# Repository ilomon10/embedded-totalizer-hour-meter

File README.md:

# Totalizer Hour Meter

An ESP32-based **engine hour meter and totalizer** for 12/24 V vehicles and machines. It counts engine run hours from the alternator signal, counts totalizer pulses, and measures vibration, roll/pitch and compass heading with an IMU. Counters survive power cuts in the ESP32's flash and the EEPROM (either one is enough), time is kept in UTC on an RTC, and everything is reported as compact [SensorFrame](sensorframe/README.md) binary frames over USB, UART or Bluetooth SPP to the `hour-meter` configurator.

Firmware version: **2.7.0** (see `kFirmwareVersion` in [`Protocol.h`](esp32/lib/App/src/Protocol.h)).

```
 Vehicle 12/24 V ──► main board ───────────────────────────────┐
 L / D+ (run)─┐      PTC + reverse diode + TVS → LM2596 (5 V)  │
 Pulse input ─┴────► PC817 isolated inputs ───► GPIO27 / GPIO26│
                                                               ▼
                    ┌──────────── ESP32 ───────────────────────────┐
                    │ AT24C256 EEPROM · DS3231 RTC · MPU-6500 IMU  │
                    │ (I2C, all optional and hot-pluggable)        │
                    └───────────────┬──────────────────────────────┘
                                    │ SensorFrame (TLV + CRC16, COBS)
                       USB / UART / Bluetooth SPP
                                    ▼
                    configurator/  hour-meter: TUI · read · commands
```

## Repository map

| Path | What it is |
|---|---|
| [`esp32/`](esp32/README.md) | PlatformIO firmware. Envs: `esp32dev` (firmware for the devboard), `can-board` (the same firmware for the main board), `bench` (module test firmware), `native` (unit tests on the PC) |
| [`configurator/`](configurator/README.md) | `hour-meter` (Bun, released as a standalone binary): full-screen TUI, live reader (`read`), single commands (`get`, `set`, ...), firmware update over USB (`firmware`) and the `DeviceClient` library |
| [`sensorframe/`](sensorframe/README.md) | The wire format: [SPEC.md](sensorframe/SPEC.md), header-only C++ library (`arduino/`), zero-dependency npm package (`js/`), shared golden test vectors |
| [`schematic/hour-meter-board/`](schematic/hour-meter-board/README.md) | Main board (KiCad): ESP32-WROOM-32E, 9–30 V supply and one Molex Micro-Fit 2 × 8 harness plug with CAN, RS232, RS485, isolated DIN1/DIN2, AIN1, DOUT1 and a 5 V sensor supply; MPU-6500 + LIS3MDL, RTC, EEPROM, USB-C, GPS and Qwiic ports. 100 × 100 mm, 2 layers, routed by hand; JLCPCB order files in `production/`, bring-up guide in `BRINGUP.md` |
| [`schematic/hour-meter-devboard/`](schematic/hour-meter-devboard/README.md) | Devboard (KiCad): 88 × 91 mm, 2-layer, through-hole carrier for ready-made modules from Indonesian shops: ESP32 DevKit V4 (USB-C), 817 opto module, GY-9250, DS3231 ZS-042, AT24C256 and a GY-271 compass. Runs from the DevKit's USB-C; Gerbers, a BOM with local shop names, LCSC lists and a 1:1 fit-check PDF in `production/` |
| [`schematic/fault-analysis/`](schematic/fault-analysis/README.md) | ngspice simulations: the main board's ports and harness (`microfit_can.py`), and supply transients, reverse polarity, shorted outputs and miswired connectors for the circuits both boards use (`faults.py`) |
| `schematic/datasets/` | Datasheets (LIS3MDL, MAX13223E) |
| [`simulator/`](simulator/README.md) | Bun device simulator: the real protocol on a virtual serial port (socat), TCP or stdio, with fault scenarios, the Bluetooth lock, and a web UI (`--web`): every value live, a 3D bench, and a truck/plane on an OpenStreetMap map with IMU-only dead reckoning. For driver development without hardware |
| `canbus/` | `can.sh`: CANable2 (slcan) helper for can-utils: `up [rate] [--tx]`, `down`, `scan [seconds]`, `status`. Listen-only by default |

Older board versions (the rev A and rev C module carriers, the rev B main board and its 2-layer, compact, LM2596, I/O and Micro-Fit versions, the auto-routed CAN board and the PSU-B supply) were removed on 2026-11-04. They are in the git history at commit d35ef2d.

## Hardware at a glance

Two boards run the same firmware:

| Board | What it is | Firmware build |
|---|---|---|
| [Main board](schematic/hour-meter-board/README.md) | everything on one PCB, made and assembled by JLCPCB: 9–30 V supply, one harness plug with CAN, RS232, RS485, DIN1/DIN2, AIN1, DOUT1 and a 5 V sensor supply, MPU-6500 + LIS3MDL IMU | `pio run -e can-board` |
| [Devboard](schematic/hour-meter-devboard/README.md) | ready-made modules on a through-hole carrier, powered from USB: ESP32 DevKit V4, 817 opto module, GY-9250, DS3231, AT24C256, GY-271 compass | `pio run -e esp32dev` (the default) |

Both: AT24C256 EEPROM (0x50) · DS3231 RTC (0x68) · MPU-6500/MPU9250 IMU (**0x69**, AD0 high) · alternator input GPIO27 · pulse input GPIO26 (through PC817 optocouplers, outputs active LOW) · Bluetooth Classic SPP (off by default, PIN-locked). The UART link is GPIO16/17 on the devboard and the RS232 port on the main board. Module wiring and the required resistor changes: [esp32/docs/WIRING.md](esp32/docs/WIRING.md).

Before ordering the main board, check part stock with `./scripts/jlc-stock.ts <bom.csv>`.

## Quick start

Prerequisites: [PlatformIO](https://platformio.org/) CLI (firmware), [Bun](https://bun.com) 1.4.4 or newer (configurator, simulator, scripts, doc checks). Optional: socat (simulator tty), Node.js ≥ 18 (only for the `sensorframe/js` npm package tests), KiCad 8+ (hardware), can-utils (`canbus/can.sh`). Users who only need the tools can download the `hour-meter` / `hour-meter-sim` binaries (Linux x64, Windows x64) from the releases page instead.

```bash
# Firmware
cd esp32
pio run -e esp32dev -t upload       # build + flash (devboard)
pio run -e can-board -t upload      # the same, for the main board

# Host tools
cd ../configurator                  # or download hour-meter from the releases page
bun install                         # once: the TUI's packages
bun run start --demo                # try the TUI with a simulated device (no hardware)
bun run start /dev/ttyUSB0          # the real device
bun run start set-time --port /dev/ttyUSB0   # set the RTC from the PC clock (UTC)
bun run start get hour --port /dev/ttyUSB0   # read the hour meter
bun run start firmware flash --port /dev/ttyUSB0   # update to the newest release (no PlatformIO needed)
```

No device at hand? `bun run start --demo` runs a simulated one inside the configurator, or `cd simulator && bun install && bun run start` creates one at `/tmp/ttyHourMeter` for any tool or driver.

Testing loose modules before soldering: `pio run -e bench -t upload`, see [TESTING-MODULES.md](esp32/docs/TESTING-MODULES.md).

## Tests and checks

```bash
cd esp32 && pio test -e native            # firmware unit tests with fake chips (ASan + UBSan)
cd esp32 && pio check -e esp32dev         # clang-tidy static analysis
./esp32/scripts/check-docs.ts             # docs, host tag table and firmware tables agree
cd configurator && bun run test           # hour-meter: commands, DeviceClient, the TUI
cd sensorframe/js && npm test             # SensorFrame JS library
make -C sensorframe/arduino/test          # SensorFrame C++ library on the desktop
cd simulator && bun run test              # simulator: firmware golden frames, frame catalog, command rules
bun test scripts/                         # release notes and asset names, JLCPCB BOM parsing
cd configurator && bun check && bun run lint && bun fmt --check   # types, lint, format (the same in simulator/)
```

## Releasing

One GitHub release, tagged `v<VERSION>` (the [`VERSION`](VERSION) file), carries all three parts: the firmware images, the `hour-meter` binaries and the `hour-meter-sim` binaries. Each part keeps its own version (`kFirmwareVersion` in `Protocol.h`, `TOOL_VERSION` in `configurator/src/version.ts`, `SIM_VERSION` in `simulator/main.ts`), and the release notes show them side by side. [`scripts/release.ts`](scripts/release.ts) does it all:

```bash
./scripts/release.ts --dry-run              # what it would run, plus the release notes; changes nothing
./scripts/release.ts                        # checks, tests, builds, asks, then tags, pushes and publishes
./scripts/release.ts --bump minor           # next release: VERSION 1.0.0 -> 1.1.0 in a commit first
./scripts/release.ts --notes notes.md --draft   # your own notes ("# Title" first line), as a draft
```

It releases HEAD (or `--ref <commit>`). It tests and builds that exact commit in a temporary git worktree, and puts the files, one `SHA256SUMS` and `NOTES.md` in `.release/v<VERSION>/`. It asks before anything leaves your machine. Afterwards it downloads the release and checks `SHA256SUMS`, both binaries' `--version` and the firmware image.

It stops before changing anything if:
- you're not on `main`;
- a released folder has uncommitted changes;
- `gh` isn't logged in;
- `origin/main` has commits you lack;
- the tag or release already exists. Use `--bump` in that case.

It warns when a part changed since the previous release but still has the same version. Without `--notes`, the notes are generated from the Conventional Commit messages since the previous release. Releases before 1.0.0 were separate per part (`firmware-v*`, `configurator-v*`, `simulator-v*`).

`hour-meter firmware` finds the firmware in a release by its file name, `hour-meter-<firmware version>-esp32dev-merged.bin`, and checks it against the release's `SHA256SUMS`. Keep both. The configurator's tests fail if `assetNames()` in `scripts/release-lib.ts` stops matching.

## Documentation

| You are… | Read |
|---|---|
| Building an app that talks to the device | [INTEGRATION-GUIDE.md](esp32/docs/INTEGRATION-GUIDE.md) + [SensorFrame SPEC.md](sensorframe/SPEC.md) |
| Writing a driver: exact bytes of every frame | [FRAME-CATALOG.md](esp32/docs/FRAME-CATALOG.md) |
| Developing without hardware | [simulator/README.md](simulator/README.md) |
| Wiring the hardware | [main board](schematic/hour-meter-board/README.md) and its [bring-up](schematic/hour-meter-board/BRINGUP.md), [devboard](schematic/hour-meter-devboard/README.md), [WIRING.md](esp32/docs/WIRING.md) (the devboard's modules) |
| Working on the firmware | [ARCHITECTURE.md](esp32/docs/ARCHITECTURE.md), [CODING-STANDARD.md](esp32/docs/CODING-STANDARD.md) |
| A TypeScript developer new to C++ | [CPP-FOR-TYPESCRIPT.md](esp32/docs/CPP-FOR-TYPESCRIPT.md) |
| Curious how data survives power cuts | [STORAGE.md](esp32/docs/STORAGE.md), [EEPROM-LAYOUT.md](esp32/docs/EEPROM-LAYOUT.md) |
| Setting up the IMU | [CALIBRATION.md](esp32/docs/CALIBRATION.md) |
| Using the TUI, CLI or Bluetooth | [configurator/README.md](configurator/README.md) |
| Using SensorFrame in another project | [sensorframe/README.md](sensorframe/README.md) |

## Design rules

- **Time is UTC only.** The device stores a Unix epoch with no timezone; host tools convert for display.
- **`esp32/lib/App/src/Protocol.h` is the single source of truth for tags.** After any protocol change, run `./esp32/scripts/check-docs.ts`, update `configurator/src/tags.ts`, port the change to `simulator/src/frames.ts`, and run `bun run test` there (it fails until the simulator's frames match the firmware's golden frames again).
- **USB is the recovery path:** fixed at 115200 baud and always accepts commands. `uartBaud` only affects the UART pins.
- **The stores (ESP32 flash, EEPROM) hold only counters, calibration and settings**, never sample logs. Filtering (Kalman) runs in RAM.

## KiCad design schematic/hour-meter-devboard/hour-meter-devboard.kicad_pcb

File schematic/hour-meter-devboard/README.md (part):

# Hour Meter devboard: ESP32 V4 module carrier with compass (rev D)

An 88 × 91 mm, 2-layer, through-hole carrier for ready-made modules from Indonesian electronics shops:
- the ESP32 DevKit V4 (USB-C, 38 pins);
- the 2-channel PC817 "817 Module";
- the GY-9250 (MPU9250/6500);
- the DS3231 ZS-042 RTC;
- the AT24C256 EEPROM;
- the GY-271 compass (QMC5883L or HMC5883L).

The DevKit's USB-C is the only supply. Vehicle wires go to screw terminals, and every other part is a common THT part.

The devboard is rev D of the module carrier: rev C plus a socket for a GY-271 compass, on a board 20 mm taller ([Changes from rev C](#changes-from-rev-c)). GY-9250 modules sold locally often carry an MPU6500, which has no compass; the GY-271 always has one. The firmware pins are those of the earlier carriers, so it runs the `esp32dev` build.

| | |
|---|---|
| Schematic | `hour-meter-devboard.kicad_sch` (PDF: `hour-meter-devboard.pdf`, picture: `hour-meter-devboard.png`) |
| PCB | `hour-meter-devboard.kicad_pcb` (pictures: `hour-meter-devboard-pcb.png`, `hour-meter-devboard-3d.png`) |
| Ready to order | `production/hour-meter-devboard-gerbers.zip` (Gerbers + drill files) |
| Parts list | `production/hour-meter-devboard-bom.csv`: what to buy, with the search terms local shops use |
| LCSC order | `production/hour-meter-devboard-lcsc-upload.csv` for LCSC's BOM tool, and `-lcsc-parts.csv` with part numbers, stock and fit notes ([Buying the parts](#buying-the-parts)) |
| Check before ordering | `production/hour-meter-devboard-fit-check-1to1.pdf`: print at 100 % and lay the modules on it |
| Custom parts | `hour-meter-modules.kicad_sym` (symbols), `hour-meter-modules.pretty/` (footprints, from `tools-gen-footprints.py`) |
| Input simulations | [fault analysis](../fault-analysis/README.md), *V4 module carrier* group |
| Firmware | `pio run -e esp32dev -t upload` in `esp32/` (the default build); module wiring and tests in [WIRING.md](../../esp32/docs/WIRING.md) |

**Checks at release (rev D, 2026-11-04, after the [hand edits and their audit](#hand-edits-and-audit)):**
- ERC: 0 errors, 0 warnings.
- DRC: 0 errors, 0 warnings, 0 unconnected, 0 schematic mismatches. JLCPCB's 2-layer limits pass too.
- 2 copper layers; the Gerbers hold copper L1/L2 only.
- Logic copper stays at least 3.8 mm from vehicle copper (the netclass minimum is 0.8 mm).

## What is on the board

| Ref | Part | Connects to |
|---|---|---|
| U1 | ESP32 DevKit V4 on 2 × 19 sockets. The antenna overhangs the top edge; the USB-C end points down | everything |
| M1 | 817 module on 4 M3 standoffs, above its own input protection | J1/J2 inputs → GPIO27/GPIO26 |
| M2, M3, M4 | DS3231, AT24C256 and GY-9250, lying flat on sockets, chip side up | I2C, 3V3 |
| M5 | GY-271 compass, lying flat on a 1×5 socket in the bottom strip, far from the DevKit and the RTC battery | I2C, 3V3; DRDY not connected |
| J1, J2 | Screw terminals: alternator (D+/L) and 12/24 V pulse; pin 2 = vehicle ground | M1 inputs |
| J3 | Spare 2 × 5 header: UART2 and five GPIOs, 3V3 through F1 | U1 |
| D5 | Status LED (green, 3 mm) | GPIO2 |

| ESP32 pin | Use | | I2C address | Device |
|---|---|---|---|---|
| GPIO21 / 22 | I2C SDA / SCL (100 kHz, module pull-ups) | | 0x50 | AT24C256 (A0–A2 = GND) |
| GPIO27 | ALT_IN, from J1 through 817 channel 1 (LOW = running) | | 0x68 | DS3231 |
| GPIO26 | PULSE_IN, from J2 through 817 channel 2 | | 0x57 | AT24C32 on the ZS-042 (unused) |
| GPIO17 / 16 | UART2 TX / RX on J3 | | 0x69 | MPU9250 / 6500 (AD0 = 3V3) |
| GPIO4, 13, 25, 32, 33 | Spare, on J3 | | 0x0C | AK8963 magnetometer (MPU9250 only) |
| GPIO2 | Status LED D5, active high. **The firmware doesn't drive it yet** | | 0x0D | QMC5883L on the GY-271 (most modules sold today) |
| | | | 0x1E | HMC5883L on older GY-271 modules |

J3, seen from the top (labels on the silkscreen, full pinout on the back):

```
upper row   2 GND    4 RX2 (IO16)   6 IO13   8 IO32   10 GND
lower row   1 3V3*   3 TX2 (IO17)   5 IO4    7 IO25    9 IO33        * through F1, 0.1 A PTC
```

J3 is for 3.3 V logic only, and nothing on it is vehicle-proof. GPIO12, 14 and 15 are left off: 12 and 15 are boot strapping pins, and 14 puts out PWM at boot.

## ⚠ Measure before you order

The module footprints use typical clone dimensions. **Print `production/hour-meter-devboard-fit-check-1to1.pdf` at 100 %** (no "fit to page"). Check that the board outline measures 88 × 91 mm, then lay each module on its outline: the pins must land on the pads. If one doesn't fit, change its numbers in `tools-gen-footprints.py` and regenerate (see [the end](#regenerating-after-a-change)).

| Part | Assumed | Check |
|---|---|---|
| ESP32 DevKit V4 | 2 × 19 pins, rows **25.4 mm apart** (Espressif's DevKitC footprint), antenna about 7 mm beyond pin 1 | Some narrow 38-pin clones use 22.86 mm |
| 817 module | 38 × 29 mm, 4 × M3 holes **32 × 24 mm** apart | Only one seller lists the hole spacing |
| GY-9250 | 15.5 × 25.5 mm, 10 pins down the left edge; M3 holes 12 mm right of the pins, 0.5 mm and 21.6 mm below pin 1 | The holes come from a photo. If they don't line up, leave the two standoffs out |
| DS3231 ZS-042 | 38 × 22 mm, 1 × 6 pins on one short edge, 32K at the top | |
| AT24C256 | About 36 × 13.5 mm, 4 pins on one short edge: GND, SDA, SCL, VCC from the top | Other boards differ: match the labels |
| GY-271 | Up to 15 × 15 mm, 5 pins: VCC, GND, SCL, SDA, DRDY from the top | Sellers list 13–15 mm; check the pin order on yours |
| F1 | 5.0 mm lead pitch | |

## Ordering the PCB

Upload `production/hour-meter-devboard-gerbers.zip` to a local PCB maker or to JLCPCB / PCBWay (both ship to Indonesia).

| Setting | Value |
|---|---|
| Layers, size | 2 layers, 88 × 91 mm, FR-4 1.6 mm, 1 oz copper |
| Finish, colour | HASL (lead-free is fine), any colour, silkscreen on both sides |
| Smallest track / gap | 0.4 mm / 0.3 mm (0.8 mm between vehicle and logic copper) |
| Smallest hole | 0.6 mm (vias, 1.2 mm pads); component holes 0.8–1.3 mm, mounting holes 3.2 mm |
| Silkscreen text | 1.0 mm and up |

These rules are coarser than most fabs need, so a local maker who can't do fine tracks can still make this board. No assembly service is needed.

## Buying the parts

Everything is in `production/hour-meter-devboard-bom.csv`, with a search term for Tokopedia, Shopee or a shop counter. Besides the five modules and the THT parts, it lists:
- the female headers: 2 × 1×20 (cut to 19), 1×6, 1×4, 1×10, 1×5;
- a 1×40 straight pin strip for re-fitting the module headers;
- 4 nylon M3 spacers (10–12 mm) for the 817 module;
- 3 nylon (or brass) M3 screws for the mounting holes: steel near the compass shifts its reading;
- hook-up wire and a CR2032.

**From LCSC, together with the JLCPCB order:** upload `production/hour-meter-devboard-lcsc-upload.csv` in LCSC's BOM tool.
- **What it covers:** every THT part, the sockets and headers, and the 817 module's nylon standoffs and screws.
- **Size:** 20 lines in quantities for 5 boards (JLCPCB makes 5 PCBs), about US$15 before shipping. Stock and prices were seen on 2026-11-04.
- **Fewer boards:** lower the quantities in the cart. Most lines are already at LCSC's minimum.
- **Details:** `-lcsc-parts.csv` gives every part's stock, its fit against the footprint, and the optional lines (P6KE18A, GY-9250 standoffs).
- **Not on LCSC:** the six modules, the CR2032 and hook-up wire. Buy those locally.

Fit notes for the LCSC parts:
- **R1, R5, R7:** 1/6 W parts with a 3.4 mm body, so the leads bend easily on the 7.62 mm footprint. They carry 2 mW at most.
- **D5:** a yellow-green GaP LED (about 2 V). From 3.3 V through 1 kΩ it gets about 1.4 mA. A 3 V "emerald" green would barely light.
- **J1, J2:** the KF128-5.08 is a true 5.08 mm part. Its pins are a snug fit in the 1.3 mm holes.

**D3/D4:** the 1N4744A (15 V, 1 W zener) suits 12 V vehicles, and 24 V vehicles whose alternator clamps load dump (all recent ones). On an older 24 V truck without that clamp, fit a **P6KE18A** TVS in the same holes instead ([simulation](../fault-analysis/README.md#results)).

## Preparing the modules

Every module lies flat, chip side up, on a standard 8.5 mm female socket. Each needs a straight pin header soldered on its underside, pointing down.

1. **817 module:** remove **both G jumpers**. With a jumper fitted, the vehicle ground and the ESP32 ground are joined and the isolation is gone ([WIRING.md](../../esp32/docs/WIRING.md#the-817-module)).
2. **DS3231 ZS-042:**
   - Remove the **charge resistor** (or its diode) beside the battery holder; a CR2032 is not rechargeable ([WIRING.md](../../esp32/docs/WIRING.md)).
   - Replace the right-angle header with a straight one on the battery side. The holder then faces the carrier; no parts sit under it.
3. **AT24C256:** set the A0, A1, A2 and WP jumpers to GND (address 0x50, writes allowed). Move its header to the underside.
4. **GY-9250:** solder its header on the underside.
5. **GY-271:** solder its 1×5 header on the underside, so the chip faces up. Most modules sold today carry a QMC5883L (marked 5883 or DA 5883); it answers at I2C address 0x0D.
6. **DevKit:** as sold.

## Assembly order

1. **Low parts first, including the ones that end up under modules:**
   - R5, R7, C1, C2 and C4 go under the DevKit; R1 goes below its USB end, under the cable plug.
   - D1–D4, R4 and R6 go under the 817 module.
   - D1/D2 (1N4007) and D3/D4 (1N4744A) look alike: check the print. The band goes to the **K** mark.
2. **The other parts:**
   - F1, then C3 (long leg to the square + pad) and D5 (long leg to the round pad);
   - J1 and J2, with the wire entry facing the board edge;
   - J3.
3. **Sockets:**
   - 2 × 1×19 for the DevKit: plug the DevKit in while you solder them, so the rows stay parallel.
   - 1×6 (M2), 1×4 (M3), 1×10 (M4) and 1×5 (M5).
4. **817 module:**
   - Solder 8 short wires (about 4 cm) into the **IN1 G IN2 G** and **V1 G V2 G** pads.
   - Mount the module on its 4 spacers.
   - Screw the wires into its terminals in the same order: inputs on the left, outputs on the right.
5. **Plug in the modules.** The pin names printed on each module must match the labels beside its socket.
6. **First power-up:**
   - Connect USB-C to a PC and open the [configurator](../../configurator/README.md) (`hour-meter /dev/ttyUSB0`).
   - Its Overview screen lists the modules and the device clock. `hour-meter read /dev/ttyUSB0 --imu` shows the IMU live.
   - Then check the inputs as in [WIRING.md](../../esp32/docs/WIRING.md#checking-it-with-a-multimeter-esp32-powered).

## In the vehicle

- **Power:** use a USB car charger with 5 V, 1 A or more, rated for 24 V if the truck is 24 V.
  - Its ground is usually the vehicle ground. The 817 module then still keeps vehicle spikes off the GPIOs, but the two grounds are no longer isolated.
- **Inputs:** J1 takes the engine-running wire (alternator D+/L or the oil-pressure switch) on pin 1 and vehicle ground on pin 2. J2 takes a 12/24 V pulse. To find the right wire, see [Pick the wire](../../esp32/docs/WIRING.md#pick-the-wire).
- **Mounting:** M3 screws in H1, H3 and H4, solidly fixed: the vibration check needs it.
  - H3 and H4 are the bottom corners, beside the compass: use nylon or brass screws there.
  - The DevKit's corner (top right) has no hole. If the box allows, rest it on a rubber pad or a standoff, so it can't shake.
  - Mount the box away from steel brackets, speakers and heavy current cables if you want a usable heading.
  - The X and Y arrows on the silkscreen show the IMU axes; level the IMU with the configurator's calibration.

## Design notes

- **Power:**
  - The DevKit's 5V pin is unused, so nothing can back-feed the USB port.
  - All modules run from the DevKit's 3V3 regulator. This keeps their I2C pull-ups at 3.3 V; the ESP32's pins are not 5 V tolerant.
  - F1 (0.1 A PTC) feeds J3's 3V3, so a short outside the box can't pull the DevKit's 3V3 down.
- **Vehicle inputs:** each input runs through D1 (reverse polarity), R4 (1.5 kΩ, 1 W, current limit) and D3 (15 V clamp) into the 817 module.
  - **Turn-on and current:** the GPIO goes LOW from about 3 V on the terminal, so a key-on charge-lamp wire (below 2 V) reads as stopped. The PC817 LED gets 1.9 mA at 12 V and 4.0 mA at 28.8 V.
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
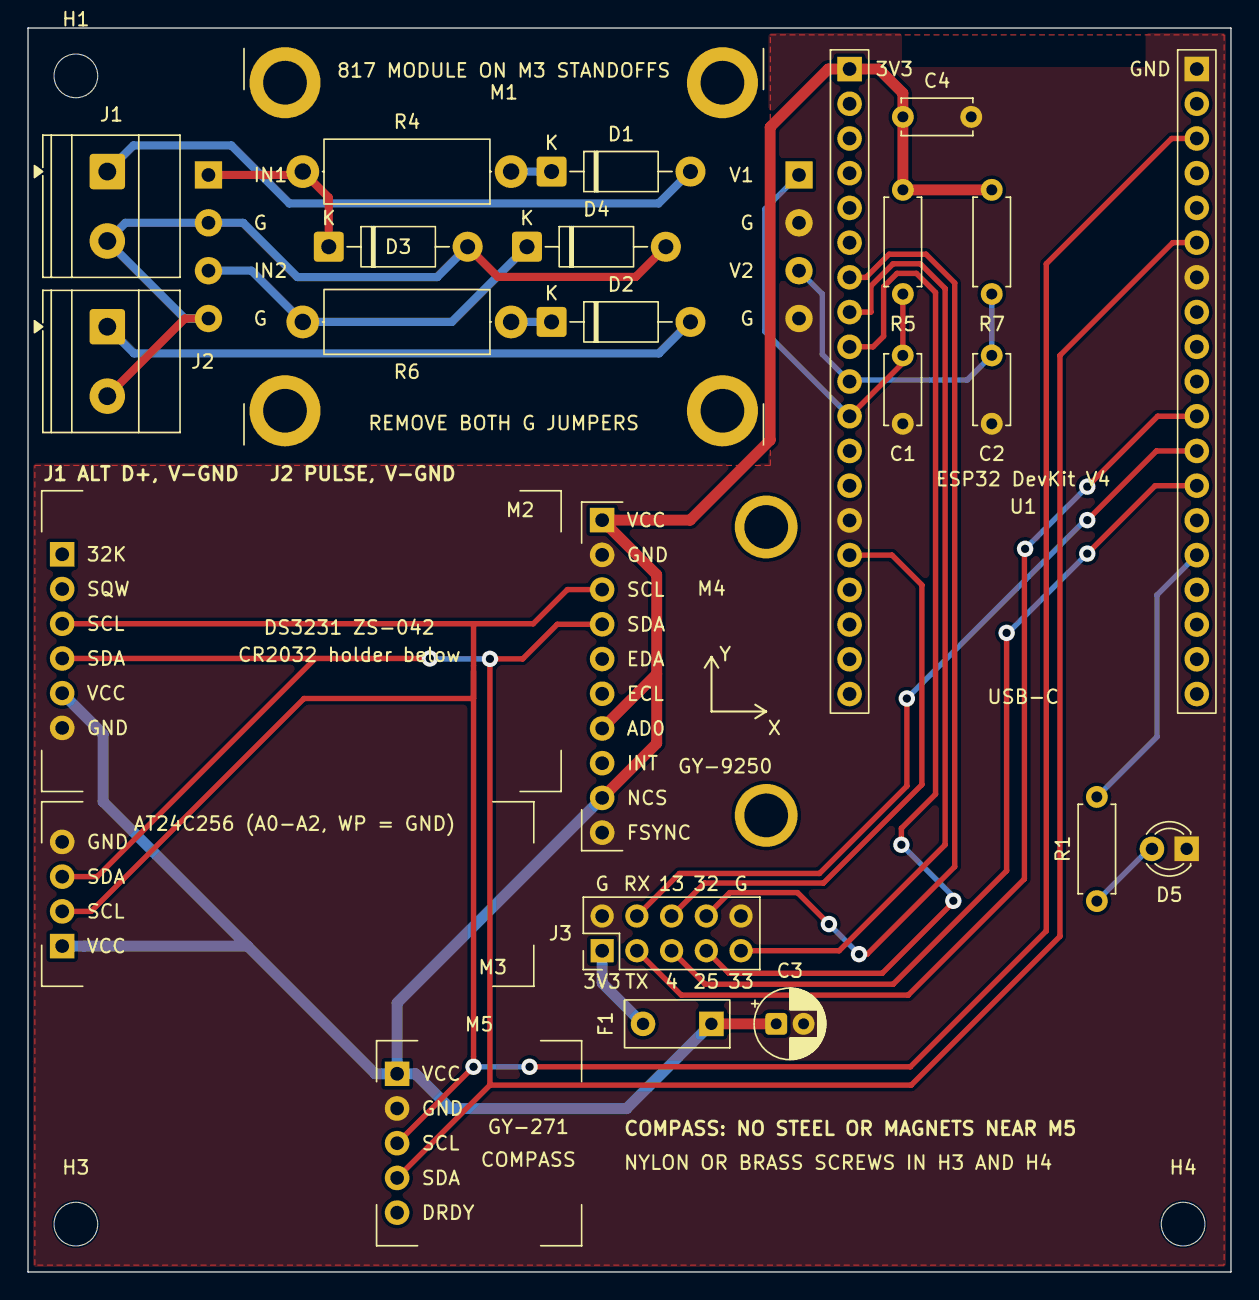
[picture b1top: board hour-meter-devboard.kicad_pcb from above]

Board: 2 copper layers, 88.0 x 91.0 mm, 27 parts (0 on the bottom side), 23 nets.

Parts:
C1, C4: 100nF; C_Disc_D5.0mm_W2.5mm_P5.00mm
C2: 1nF; C_Disc_D5.0mm_W2.5mm_P5.00mm
C3: 10uF 16V; CP_Radial_D5.0mm_P2.00mm
D1, D2: 1N4007; D_DO-41_SOD81_P10.16mm_Horizontal
D3, D4: 1N4744A (15V 1W); D_DO-41_SOD81_P10.16mm_Horizontal
D5: LED 3mm green; LED_D3.0mm
F1: PTC 0.1A 60V; PTC_Radial_P5.00mm
H1, H3, H4: MountingHole_3.2mm_M3
J1: ALTERNATOR; TerminalBlock_Phoenix_MKDS-1,5-2-5.08_1x02_P5.08mm_Horizont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
J2: PULSE 12/24V; TerminalBlock_Phoenix_MKDS-1,5-2-5.08_1x02_P5.08mm_Horizont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
J3: SPARE GPIO 3.3V; PinHeader_2x05_P2.54mm_Vertical
M1: 817 Module 2CH (remove G jumpers); Module_PC817_2CH_Stacked
M2: DS3231 RTC module (ZS-042); Module_DS3231_ZS042_Flat
M3: AT24C256 EEPROM module (A0-A2, WP = GND: 0x50); Module_AT24C256_Flat
M4: MPU9250 module (AD0 = 3V3, 0x69); Module_MPU9250_GY9250_Flat
M5: GY-271 compass module (QMC5883L 0x0D / HMC5883L 0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; Module_GY271_Flat
R1: 1k; R_Axial_DIN0207_L6.3mm_D2.5mm_P7.62mm_Horizontal
R4, R6: 1.5k 1W; R_Axial_DIN0414_L11.9mm_D4.5mm_P15.24mm_Horizontal
R5, R7: 47k; R_Axial_DIN0207_L6.3mm_D2.5mm_P7.62mm_Horizontal
U1: ESP32 DevKit V4 Type-C (38-pin); ESP32_DevKitC_V4_38pin_Socket

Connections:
+3V3: C3.1, C4.1, F1.1, M2.5, M3.1, M4.1, M4.7, M4.9, M5.1, R5.1, R7.1, U1.1
/+3V3_EXT: F1.2, J3.1
/ALT_IN: C1.1, M1.5, R5.2, U1.11
/I2C_SCL: M2.3, M3.2, M4.3, M5.3, U1.22
/I2C_SDA: M2.4, M3.3, M4.4, M5.4, U1.25
/IO4: J3.5, U1.32
/IO13: J3.6, U1.15
/IO25: J3.7, U1.9
/IO32: J3.8, U1.7
/IO33: J3.9, U1.8
/LED: R1.1, U1.34
/OPTO1: D3.1, M1.1, R4.2
/OPTO2: D4.1, M1.3, R6.2
/PULSE_IN: C2.1, M1.7, R7.2, U1.10
/UART_RX: J3.4, U1.31
/UART_TX: J3.3, U1.30
/VEH_GND: D3.2, D4.2, J1.2, J2.2, M1.2, M1.4
GND: C1.2, C2.2, C3.2, C4.2, D5.1, J3.2, J3.10, M1.6, M1.8, M2.6, M3.4, M4.2, M4.10, M5.2, U1.14, U1.20, U1.26
unnamed: D1.2, J1.1
unnamed: D1.1, R4.1
unnamed: D2.2, J2.1
unnamed: D2.1, R6.1
unnamed: D5.2, R1.2

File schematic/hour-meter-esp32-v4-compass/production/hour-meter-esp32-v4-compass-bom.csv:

References,Qty,Part,Search term (Tokopedia / Shopee / shop),Note,Schematic value,Footprint
"C1, C4",2,Ceramic capacitor 100 nF 50 V (104),kapasitor keramik 104,,100nF,C_Disc_D5.0mm_W2.5mm_P5.00mm
C2,1,Ceramic capacitor 1 nF 50 V (102),kapasitor keramik 102,,1nF,C_Disc_D5.0mm_W2.5mm_P5.00mm
C3,1,"Electrolytic capacitor 10 uF 16 V or 25 V, 5 mm",elco 10uF 16V,Long leg (+) to the square pad,10uF 16V,CP_Radial_D5.0mm_P2.00mm
"D1, D2",2,1N4007 rectifier diode,dioda 1N4007,Band (cathode) toward the K mark,1N4007,D_DO-41_SOD81_P10.16mm_Horizontal
"D3, D4",2,1N4744A zener 15 V 1 W,dioda zener 15V 1W 1N4744A,Old 24 V trucks without load-dump protection: P6KE18A TVS in the same holes,1N4744A (15V 1W),D_DO-41_SOD81_P10.16mm_Horizontal
D5,1,LED 3 mm green,LED 3mm hijau,Long leg (anode) to the round pad,LED 3mm green,LED_D3.0mm
F1,1,"PTC resettable fuse 0.1 A 60 V, 5 mm pitch (MF-R010 / JK60-010)",PTC resettable fuse 0.1A 60V,,PTC 0.1A 60V,PTC_Radial_P5.00mm
"J1, J2",2,"Screw terminal 2 pin, 5.08 mm (KF301-2P)",terminal block KF301 2P 5.08,Wire entry toward the board edge,ALTERNATOR / PULSE 12/24V,"TerminalBlock_Phoenix_MKDS-1,5-2-5.08_1x02_P5.08mm_Horizontal"
J3,1,"Pin header 2x5, 2.54 mm, straight",pin header male 2x5 2.54,Cut from a 2x40 strip,SPARE GPIO 3.3V,PinHeader_2x05_P2.54mm_Vertical
M1,1,2-channel PC817 isolation module (817 Module),modul optocoupler PC817 2 channel,Remove both G jumpers; mounts on 4 M3 standoffs,817 Module 2CH (remove G jumpers),Module_PC817_2CH_Stacked
M2,1,DS3231 RTC module ZS-042 + CR2032,modul RTC DS3231 ZS-042,Remove its charge resistor; solder a straight 1x6 header underneath,DS3231 RTC module (ZS-042),Module_DS3231_ZS042_Flat
M3,1,AT24C256 I2C EEPROM module,modul EEPROM AT24C256 I2C,A0-A2 and WP jumpers to GND; solder a straight 1x4 header underneath,"AT24C256 EEPROM module (A0-A2, WP = GND: 0x50)",Module_AT24C256_Flat
M4,1,GY-9250 (MPU9250 or MPU6500) module,modul GY-9250 MPU9250,"Straight 1x10 header underneath, chip side up","MPU9250 module (AD0 = 3V3, 0x69)",Module_MPU9250_GY9250_Flat
M5,1,GY-271 compass module (QMC5883L or HMC5883L),modul kompas GY-271 QMC5883L,"Straight 1x5 header underneath (usually supplied), chip side up; no steel or magnets near it",GY-271 compass module (QMC5883L 0x0D / HMC5883L 0x1E),Module_GY271_Flat
R1,1,Resistor 1 kohm 1/4 W,resistor 1K 1/4W,,1k,R_Axial_DIN0207_L6.3mm_D2.5mm_P7.62mm_Horizontal
"R4, R6",2,Resistor 1.5 kohm 1 W metal film,resistor 1K5 1W,,1.5k 1W,R_Axial_DIN0414_L11.9mm_D4.5mm_P15.24mm_Horizontal
"R5, R7",2,Resistor 47 kohm 1/4 W,resistor 47K 1/4W,,47k,R_Axial_DIN0207_L6.3mm_D2.5mm_P7.62mm_Horizontal
U1,1,"ESP32 DevKit V4, USB-C, 38 pins (ESP32-WROOM-32D/E)",ESP32 DevKit V4 Type C 38 pin,Check its pin rows are 25.4 mm apart (fit-check PDF),ESP32 DevKit V4 Type-C (38-pin),ESP32_DevKitC_V4_38pin_Socket
,2,"Female header 1x20, 2.54 mm (cut to 19)",female header 1x20 2.54,U1 sockets,,
,1,"Female header 1x6, 2.54 mm",female header 1x6 2.54,M2 socket,,
,1,"Female header 1x4, 2.54 mm",female header 1x4 2.54,M3 socket,,
,1,"Female header 1x10, 2.54 mm",female header 1x10 2.54,M4 socket,,
,1,"Female header 1x5, 2.54 mm",female header 1x5 2.54,M5 socket,,
,1,"Pin header 1x40, 2.54 mm, straight",pin header male 1x40 2.54,Cut 6 + 4 for the M2 and M3 modules,,
,4,"Nylon M3 spacer 10-12 mm, with M3 screws",spacer nylon M3 10mm,M1 standoffs; parts underneath are up to 6 mm tall,,
,2,"Nylon M3 spacer 11 mm (or 10 mm + washer), with nylon M3 screws",spacer nylon M3 11mm,"Optional: holds the GY-9250 rigid. Nylon, like everything near the compass",,
,1,"Hook-up wire 22-24 AWG, about 30 cm",kabel jumper 22 AWG,8 short wires from the M1 pads to the 817 module terminals,,
,1,CR2032 coin cell (or LIR2032 with the charge resistor kept),baterai CR2032,RTC backup,,
,3,Nylon (or brass) M3 screws and spacers for the enclosure,baut nylon M3 + spacer nylon,"H1, H3, H4. Steel screws in H3/H4 would disturb the compass",,

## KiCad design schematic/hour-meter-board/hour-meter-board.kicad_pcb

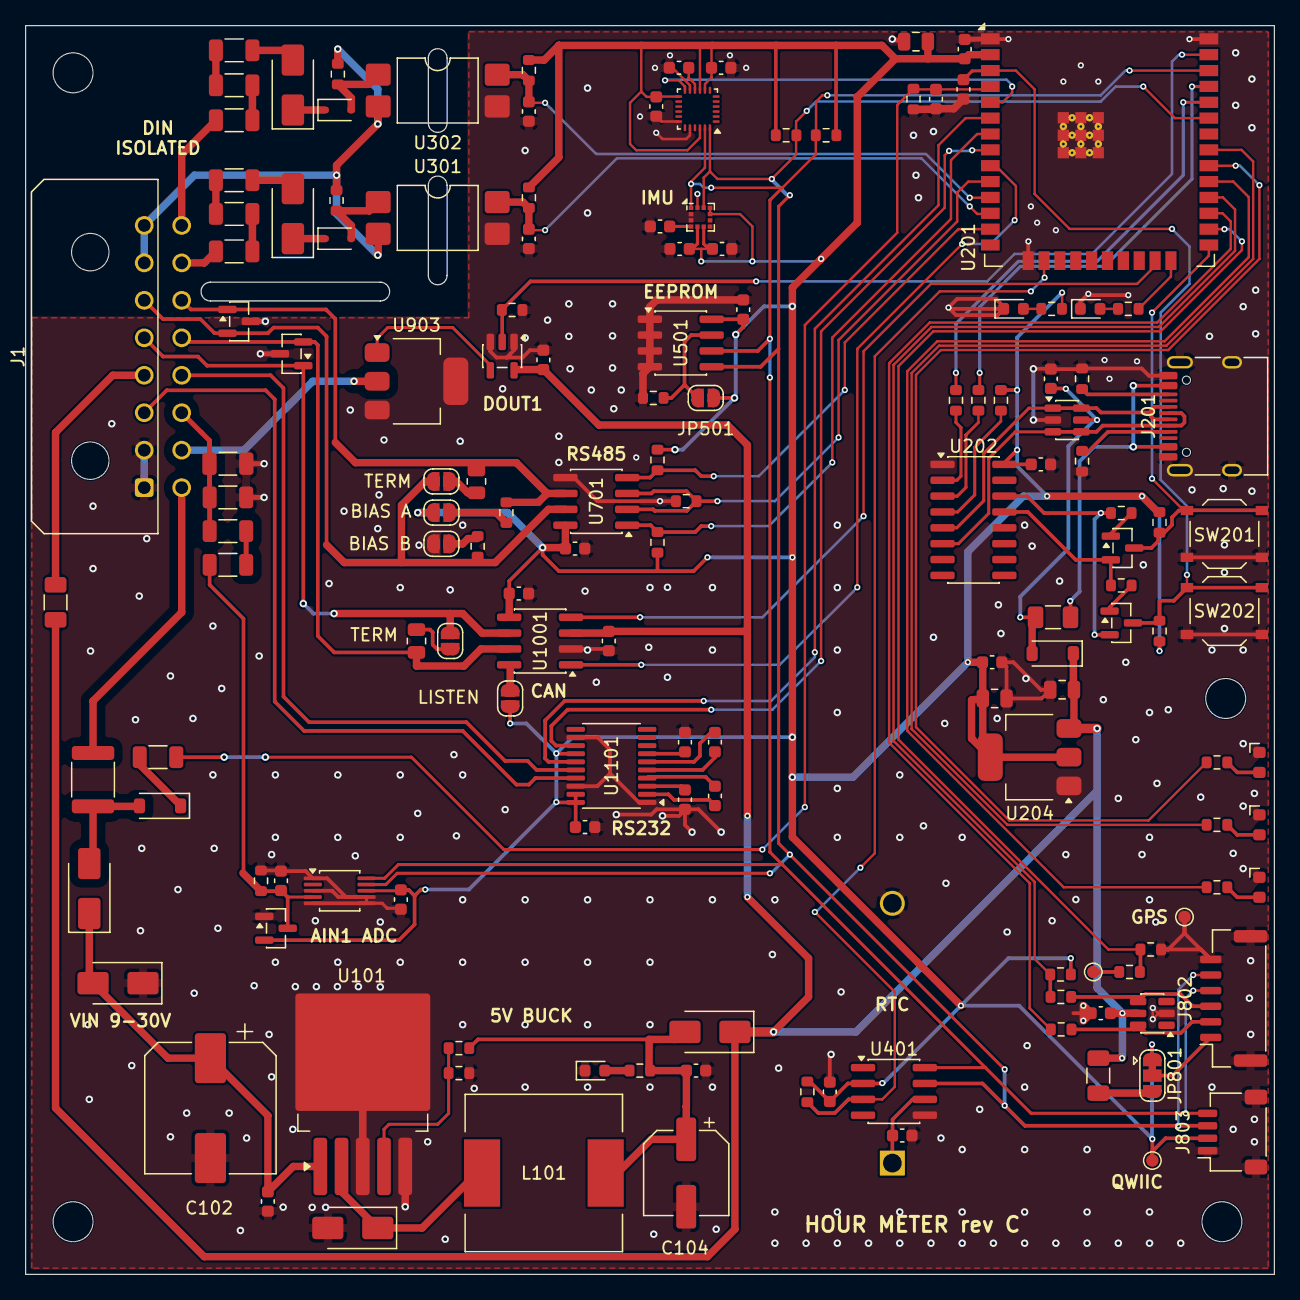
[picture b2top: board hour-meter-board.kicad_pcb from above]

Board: 2 copper layers, 100.0 x 100.0 mm, 152 parts (1 on the bottom side), 100 nets.

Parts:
BT401: CR2032; BatteryHolder_MYOUNG_BS-07-A1BJ001_CR2032
C101, C105, C202, C204, C207, C301, C401, C402, C501, C601, C603, C605, C606, C701, C802, C902, C903, C904, C1001, C1002, C1101, C1102, C1103, C1105: 100nF; C_0603_1608Metric
C102: 220uF 50V; CP_Elec_10x10
C103: 100nF 50V; C_0603_1608Metric
C104: 220uF 16V; CP_Elec_6.3x7.7
C201, C205: 10uF 25V; C_0805_2012Metric
C203, C208, C604, C1104: 1uF; C_0603_1608Metric
C206: 22uF; C_0805_2012Metric
C302: 1nF; C_0603_1608Metric
C602: 10nF; C_0603_1608Metric
C901: 10nF 1kV; C_1206_3216Metric
D101: SS34; D_SMA
D102: 1N4148W; D_SOD-123
D103, D105: SS54; D_SMA
D104: SMAJ30CA; D_SMA
D106: PWR red; LED_0603_1608Metric
D201: B5819W; D_SOD-123
D202: PWR (red); LED_0603_1608Metric
D203: STATUS (yellow); LED_0603_1608Metric
D301, D303: M7; D_SMA
D302, D304: BZT52C4V7S; D_SOD-323
D701, D1001: SZNUP3105LT1G; SOT-23
D801: P1 (green); LED_Kingbright_APA1606_1.6x0.6mm_Horizontal
D802: P2 (green); LED_Kingbright_APA1606_1.6x0.6mm_Horizontal
D803: USER (green); LED_Kingbright_APA1606_1.6x0.6mm_Horizontal
D901: BAV99; SOT-23
F101: 0.5A 60V; Fuse_1812_4532Metric
F201: 0.5A 6V; Fuse_1206_3216Metric
F801, F803: 0.2A; Fuse_1206_3216Metric
H102, H103, H104, H105: M3; MountingHole_3.2mm_M3
J1: Micro-Fit 3.0 2x8; Molex_Micro-Fit_3.0_43045-1600_2x08_P3.00mm_Horizontal
J201: USB-C; USB_C_Receptacle_HRO_TYPE-C-31-M-12
J802: GPS (GH 6-pin); JST_GH_SM06B-GHS-TB_1x06-1MP_P1.25mm_Horizontal
J803: QWIIC; JST_SH_SM04B-SRSS-TB_1x04-1MP_P1.00mm_Horizontal
JP501: WP; SolderJumper-2_P1.3mm_Open_RoundedPad1.0x1.5mm
JP702: TERM 120R; SolderJumper-2_P1.3mm_Open_RoundedPad1.0x1.5mm
JP703: BIAS A; SolderJumper-2_P1.3mm_Open_RoundedPad1.0x1.5mm
JP704: BIAS B; SolderJumper-2_P1.3mm_Open_RoundedPad1.0x1.5mm
JP801: GPS VCC 3V3/5V; SolderJumper-3_P1.3mm_Bridged12_RoundedPad1.0x1.5mm
JP1001: CAN TERM 120R; SolderJumper-2_P1.3mm_Open_RoundedPad1.0x1.5mm
JP1002: CAN LISTEN-ONLY; SolderJumper-2_P1.3mm_Open_RoundedPad1.0x1.5mm
L101: 33uH 3A; L_12x12mm_H8mm
Q201, Q202: MMBT3904; SOT-23
R101: 100k; R_1206_3216Metric
R102: 5.6k; R_0603_1608Metric
R103: 3.3k; R_0603_1608Metric
R104, R209, R210: 1k; R_0603_1608Metric
R105: 2.2k; R_0603_1608Metric
R201, R202, R205, R206, R401, R501, R701, R702, R703: 10k; R_0603_1608Metric
R203, R204: 470R; R_0603_1608Metric
R207, R208: 5.1k; R_0603_1608Metric
R211, R212, R304, R309: 4.7k; R_0603_1608Metric
R213: 0R; R_0603_1608Metric
R301, R302, R303, R306, R307, R308: 1k; R_1206_3216Metric
R305, R310: 22k; R_0603_1608Metric
R704, R1001: 120R; R_0805_2012Metric
R705, R706, R808, R809, R810: 330R; R_0603_1608Metric
R803, R804, R805: 100R; R_0603_1608Metric
R806, R807, R905: 100k; R_0603_1608Metric
R901, R902: 49.9k 0.1%; R_1206_3216Metric
R903: 10k 0.1%; R_0603_1608Metric
R904: 120R 0.1% DNP; R_1206_3216Metric
SW201: RESET; SW_Push_1P1T_XKB_TS-1187A
SW202: BOOT; SW_Push_1P1T_XKB_TS-1187A
TP801: PPS; TestPoint_Pad_D1.0mm
TP807: +3V3; TestPoint_Pad_D1.0mm
TP808: GND; TestPoint_Pad_D1.0mm
U101: LM2596S-ADJ; TO-263-5_TabPin3
U201: ESP32-WROOM-32E-N4; ESP32-WROOM-32E
U202: CH340C; SOIC-16_3.9x9.9mm_P1.27mm
U203: USBLC6-2SC6; SOT-23-6
U204: AMS1117-3.3; SOT-223-3_TabPin2
U301, U302: PC817C-S; SMDIP-4_W9.53mm
U401: DS3231MZ+TRL; SOIC-8_3.9x4.9mm_P1.27mm
U501: AT24C256C-SSHL-T; SOIC-8_3.9x4.9mm_P1.27mm
U601: MPU-6500; InvenSense_QFN-24_3x3mm_P0.4mm
U602: LIS3MDLTR; LGA-12_2x2mm_P0.5mm
U701: THVD2410DR; SOIC-8_3.9x4.9mm_P1.27mm
U802: SRV05-4; SOT-23-6
U901: ADS1115IDGST; TSSOP-10_3x3mm_P0.5mm
U902: SN74AHCT1G125DBVR; SOT-23-5
U903: BSP75N; SOT-223
U1001: TJA1051T/3; SOIC-8_3.9x4.9mm_P1.27mm
U1101: MAX13223E; TSSOP-20_4.4x6.5mm_P0.65mm

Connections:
+3V3: C201.1, C202.1, C204.1, C206.1, C207.1, C401.1, C501.1, C601.1, C602.1, C604.1, C605.1, C701.1, C903.1, C1002.1, C1105.1, D901.2, J803.2, JP501.2, JP703.1, JP801.1, JP1002.1, R201.1, R202.1, R209.1, R211.1, R212.1, R213.1, R305.1, R310.1, R401.1, R701.1, R702.1, R806.1, TP807.1, U201.2, U202.16, U204.2, U401.2, U501.8, U601.8, U601.9, U601.13, U601.22, U602.5, U602.6, U602.9, U602.10, U701.8, U901.8, U1001.5, U1101.14, U1101.19, U1101.20
+5V: C205.1, C802.1, C904.1, C1001.1, D101.1, D201.1, F801.1, F803.1, U204.3, U802.5, U902.5, U1001.3
/5V buck (U101)/+5V_PSU: C104.1, C105.1, D101.2, L101.2, R103.1, R105.1
/5V buck (U101)/LM_FB: R103.2, R104.1, U101.4
/5V buck (U101)/LM_SW: D105.1, L101.1, U101.2
/AIN1 front end/AIN1_MID: R901.2, R902.1
/AIN1_ADC: C902.1, D901.3, R902.2, R903.1, U901.4
/AIN1_RAW: C901.1, J1.11, R901.1, R904.1
/CAN_H: D1001.2, J1.13, R1001.1, U1001.7
/CAN_L: D1001.1, J1.5, JP1001.1, U1001.6
/CAN_RX: U201.23, U1001.4
/CAN_TX: U201.9, U1001.1
/DIN1_IN_N: C301.1, R305.2, U201.12, U301.4
/DIN1_RAW: J1.15, R301.1
/DIN2_IN_N: C302.1, R310.2, U201.11, U302.4
/DIN2_RAW: J1.16, R306.1
/DIN inputs/DIN1_D: D301.1, D302.1
/DIN inputs/DIN1_LED: D302.2, R304.1, U301.1
/DIN inputs/DIN1_R: D301.2, R303.2
/DIN inputs/DIN2_D: D303.1, D304.1
/DIN inputs/DIN2_LED: D304.2, R309.1, U302.1
/DIN inputs/DIN2_R: D303.2, R308.2
/DOUT1: J1.10, U903.2
/DOUT1 (U903)/DOUT1_IN: U902.4, U903.1
/DOUT1_CTRL: R905.1, U201.37, U902.2
/EEPROM (U501)/EE_WP: JP501.1, R501.1, U501.7
/ESP32 + USB (U201)/CH_RXD: R204.1, U202.3
/ESP32 + USB (U201)/CH_TXD: R203.1, U202.2
/ESP32 + USB (U201)/CH_V3: R213.2, U202.4
/ESP32 + USB (U201)/DTR_N: Q202.2, R205.1, U202.13
/ESP32 + USB (U201)/ESP_EN: C203.1, Q201.3, R201.2, SW201.1, U201.3
/ESP32 + USB (U201)/ESP_IO0: Q202.3, R202.2, SW202.1, U201.25
/ESP32 + USB (U201)/LED_STATUS: R210.1, U201.24
/ESP32 + USB (U201)/RTS_N: Q201.2, R206.1, U202.14
/ESP32 + USB (U201)/U0RXD: R203.2, U201.34
/ESP32 + USB (U201)/U0TXD: R204.2, U201.35
/ESP32 + USB (U201)/USB_DM: J201.A7, J201.B7, U202.6, U203.3, U203.4
/ESP32 + USB (U201)/USB_DP: J201.A6, J201.B6, U202.5, U203.1, U203.6
/ESP32 + USB (U201)/VBUS: C208.1, D201.2, F201.2, U203.5
/ESP32 + USB (U201)/VBUS_IN: F201.1, J201.A4, J201.A9, J201.B4, J201.B9
/EXP_IO5: R810.1, U201.29
/EXP_IO18: R808.1, U201.30
/EXP_IO19: R809.1, U201.31
/GPS + Qwiic/GPS_5V: F803.2, JP801.3
/GPS + Qwiic/GPS_PPS_EXT: R805.1, TP801.1
/GPS + Qwiic/GPS_RX_EXT: J802.2, R804.1, U802.6
/GPS + Qwiic/GPS_TX_EXT: J802.3, R803.1, U802.4
/GPS + Qwiic/GPS_VCC: J802.1, JP801.2
/GPS_PPS: R805.2, R807.1, U201.26
/GPS_RXD: R804.2, U201.27
/GPS_TXD: R803.2, R806.2, U201.28
/I2C_SCL: J802.4, J803.4, R212.2, U201.36, U401.8, U501.6, U601.23, U602.1, U901.10
/I2C_SDA: J802.5, J803.3, R211.2, U201.33, U401.7, U501.5, U601.24, U602.11, U901.9
/IMU_INT: U201.5, U601.12
/RS232 (U1101)/C1N: C1101.2, U1101.4
/RS232 (U1101)/C1P: C1101.1, U1101.2
/RS232 (U1101)/C2N: C1102.2, U1101.6
/RS232 (U1101)/C2P: C1102.1, U1101.5
/RS232 (U1101)/VN: C1104.1, U1101.7
/RS232 (U1101)/VP: C1103.1, U1101.3
/RS232_RXD: J1.12, U1101.16
/RS232_TXD: J1.3, U1101.17
/RS485 (U701)/BIAS_A: JP703.2, R705.1
/RS485 (U701)/BIAS_B: JP704.1, R706.2
/RS485 (U701)/TERM_A: JP702.1, R704.2
/RS485_A: D701.1, J1.14, R704.1, R705.2, U701.6
/RS485_B: D701.2, J1.6, JP702.2, R706.1, U701.7
/RS485_DE: R703.1, U201.10, U701.2, U701.3
/RS485_RX: R701.2, U201.7, U701.1
/RS485_TX: R702.2, U201.13, U701.4
/RTC (U401)/RTC_VBAT: BT401.1, C402.1, U401.6
/RTC_INT: R401.2, U201.16, U401.3
/SENSOR_5V: F801.2, J1.4
/UART2_RX: U201.6, U1101.15
/UART2_TX: U201.8, U1101.13
/VEH_GND: J1.7, J1.8, R304.2, R309.2, U301.2, U302.2
/VIN input/VIN_RAW: D102.2, D103.2, F101.2
/VIN_IN: F101.1, J1.9
/VIN_LM: C102.1, C103.1, D103.1, D104.2, U101.1
/VIN_SENSE: C101.1, R101.2, R102.1, U201.4
GND: BT401.2, C101.2, C102.2, C103.2, C104.2, C105.2, C201.2, C202.2, C203.2, C204.2, C205.2, C206.2, C207.2, C208.2, C301.2, C302.2, C401.2, C402.2, C501.2, C601.2, C602.2, C603.2, C604.2, C605.2, C606.2, C701.2, C802.2, C901.2, C902.2, C903.2, C904.2, C1001.2, C1002.2, C1103.2, C1104.2, C1105.2, D104.1, D105.2, D106.1, D202.1, D203.1, D701.3, D801.1, D802.1, D803.1, D901.1, D1001.3, J1.1, J1.2, J201.A1, J201.A12, J201.B1, J201.B12, J201.SH, J802.6, J802.MP, J803.1, J803.MP, JP704.2, R102.2, R104.2, R207.2, R208.2, R501.2, R703.2, R807.2, R903.2, R904.2, R905.2, SW201.2, SW202.2, TP808.1, U101.3, U101.5, U201.1, U201.15, U201.38, U201.39, U202.1, U203.2, U204.1, U301.3, U302.3, U401.5, U501.1, U501.2, U501.3, U501.4, U601.11, U601.18, U601.20, U602.2, U602.3, U602.12, U701.5, U802.2, U901.1, U901.3, U901.5, U901.6, U901.7, U902.1, U902.3, U903.3, U903.4, U1001.2, U1101.1, U1101.12, U1101.18
unnamed: D102.1, R101.1
unnamed: D106.2, R105.2
unnamed: D202.2, R209.2
unnamed: D203.2, R210.2
unnamed: D801.2, R808.2
unnamed: D802.2, R809.2
unnamed: D803.2, R810.2
unnamed: J201.A5, R207.1
unnamed: J201.B5, R208.1
unnamed: JP1001.2, R1001.2
unnamed: JP1002.2, U1001.8
unnamed: Q201.1, R205.2
unnamed: Q202.1, R206.2
unnamed: R301.2, R302.1
unnamed: R302.2, R303.1
unnamed: R306.2, R307.1
unnamed: R307.2, R308.1
unnamed: C603.1, U601.10
unnamed: C606.1, U602.4

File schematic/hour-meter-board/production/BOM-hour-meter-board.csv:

Comment,Designator,Footprint,LCSC,Qty
CR2032,BT401,Battery:BatteryHolder_MYOUNG_BS-07-A1BJ001_CR2032,C2979167,1
100nF,"C101,C105,C202,C204,C207,C301,C401,C402,C501,C601,C603,C605,C606,C701,C802,C902,C903,C904,C1001,C1002,C1101,C1102,C1103,C1105",Capacitor_SMD:C_0603_1608Metric,C14663,24
220uF 50V,C102,Capacitor_SMD:CP_Elec_10x10,C2887271,1
100nF 50V,C103,Capacitor_SMD:C_0603_1608Metric,C14663,1
220uF 16V,C104,Capacitor_SMD:CP_Elec_6.3x7.7,C2887273,1
10uF 25V,"C201,C205",Capacitor_SMD:C_0805_2012Metric,C15850,2
1uF,"C203,C208,C604,C1104",Capacitor_SMD:C_0603_1608Metric,C15849,4
22uF,C206,Capacitor_SMD:C_0805_2012Metric,C45783,1
1nF,C302,Capacitor_SMD:C_0603_1608Metric,C1588,1
10nF,C602,Capacitor_SMD:C_0603_1608Metric,C57112,1
10nF 1kV,C901,Capacitor_SMD:C_1206_3216Metric,C9194,1
SS34,D101,Diode_SMD:D_SMA,C8678,1
1N4148W,D102,Diode_SMD:D_SOD-123,C81598,1
SS54,"D103,D105",Diode_SMD:D_SMA,C22452,2
SMAJ30CA,D104,Diode_SMD:D_SMA,C110043,1
PWR red,D106,LED_SMD:LED_0603_1608Metric,C2286,1
B5819W,D201,Diode_SMD:D_SOD-123,C8598,1
PWR (red),D202,LED_SMD:LED_0603_1608Metric,C2286,1
STATUS (yellow),D203,LED_SMD:LED_0603_1608Metric,C2287,1
M7,"D301,D303",Diode_SMD:D_SMA,C82443,2
BZT52C4V7S,"D302,D304",Diode_SMD:D_SOD-323,C22611,2
SZNUP3105LT1G,"D701,D1001",Package_TO_SOT_SMD:SOT-23,C233434,2
P1 (green),D801,LED_SMD:LED_Kingbright_APA1606_1.6x0.6mm_Horizontal,C364567,1
P2 (green),D802,LED_SMD:LED_Kingbright_APA1606_1.6x0.6mm_Horizontal,C364567,1
USER (green),D803,LED_SMD:LED_Kingbright_APA1606_1.6x0.6mm_Horizontal,C364567,1
BAV99,D901,Package_TO_SOT_SMD:SOT-23,C68983,1
0.5A 60V,F101,Fuse:Fuse_1812_4532Metric,C19078719,1
0.5A 6V,F201,Fuse:Fuse_1206_3216Metric,C69688,1
0.2A,"F801,F803",Fuse:Fuse_1206_3216Metric,C20984,2
Micro-Fit 3.0 2x8,J1,Connector_Molex:Molex_Micro-Fit_3.0_43045-1600_2x08_P3.00mm_Horizontal,C277731,1
USB-C,J201,Connector_USB:USB_C_Receptacle_HRO_TYPE-C-31-M-12,C165948,1
GPS (GH 6-pin),J802,Connector_JST:JST_GH_SM06B-GHS-TB_1x06-1MP_P1.25mm_Horizontal,C133065,1
QWIIC,J803,Connector_JST:JST_SH_SM04B-SRSS-TB_1x04-1MP_P1.00mm_Horizontal,C160404,1
33uH 3A,L101,Inductor_SMD:L_12x12mm_H8mm,C9400,1
MMBT3904,"Q201,Q202",Package_TO_SOT_SMD:SOT-23,C20526,2
100k,R101,Resistor_SMD:R_1206_3216Metric,C17900,1
5.6k,R102,Resistor_SMD:R_0603_1608Metric,C23189,1
3.3k,R103,Resistor_SMD:R_0603_1608Metric,C22978,1
1k,"R104,R209,R210",Resistor_SMD:R_0603_1608Metric,C21190,3
2.2k,R105,Resistor_SMD:R_0603_1608Metric,C4190,1
10k,"R201,R202,R205,R206,R401,R501,R701,R702,R703",Resistor_SMD:R_0603_1608Metric,C25804,9
470R,"R203,R204",Resistor_SMD:R_0603_1608Metric,C23179,2
5.1k,"R207,R208",Resistor_SMD:R_0603_1608Metric,C23186,2
4.7k,"R211,R212,R304,R309",Resistor_SMD:R_0603_1608Metric,C23162,4
0R,R213,Resistor_SMD:R_0603_1608Metric,C21189,1
1k,"R301,R302,R303,R306,R307,R308",Resistor_SMD:R_1206_3216Metric,C4410,6
22k,"R305,R310",Resistor_SMD:R_0603_1608Metric,C31850,2
120R,"R704,R1001",Resistor_SMD:R_0805_2012Metric,C17437,2
330R,"R705,R706,R808,R809,R810",Resistor_SMD:R_0603_1608Metric,C23138,5
100R,"R803,R804,R805",Resistor_SMD:R_0603_1608Metric,C22775,3
100k,"R806,R807,R905",Resistor_SMD:R_0603_1608Metric,C25803,3
49.9k 0.1%,"R901,R902",Resistor_SMD:R_1206_3216Metric,C706414,2
10k 0.1%,R903,Resistor_SMD:R_0603_1608Metric,C95204,1
RESET,SW201,Button_Switch_SMD:SW_Push_1P1T_XKB_TS-1187A,C318884,1
BOOT,SW202,Button_Switch_SMD:SW_Push_1P1T_XKB_TS-1187A,C318884,1
LM2596S-ADJ,U101,Package_TO_SOT_SMD:TO-263-5_TabPin3,C347423,1
ESP32-WROOM-32E-N4,U201,RF_Module:ESP32-WROOM-32E,C701341,1
CH340C,U202,Package_SO:SOIC-16_3.9x9.9mm_P1.27mm,C84681,1
USBLC6-2SC6,U203,Package_TO_SOT_SMD:SOT-23-6,C7519,1
AMS1117-3.3,U204,Package_TO_SOT_SMD:SOT-223-3_TabPin2,C6186,1
PC817C-S,"U301,U302",Package_DIP:SMDIP-4_W9.53mm,C3008369,2
DS3231MZ+TRL,U401,Package_SO:SOIC-8_3.9x4.9mm_P1.27mm,C107410,1
AT24C256C-SSHL-T,U501,Package_SO:SOIC-8_3.9x4.9mm_P1.27mm,C6482,1
MPU-6500,U601,Sensor_Motion:InvenSense_QFN-24_3x3mm_P0.4mm,C50278,1
LIS3MDLTR,U602,Package_LGA:LGA-12_2x2mm_P0.5mm,C478483,1
THVD2410DR,U701,Package_SO:SOIC-8_3.9x4.9mm_P1.27mm,C1849398,1
SRV05-4,U802,Package_TO_SOT_SMD:SOT-23-6,C85364,1
ADS1115IDGST,U901,Package_SO:TSSOP-10_3x3mm_P0.5mm,C468683,1
SN74AHCT1G125DBVR,U902,Package_TO_SOT_SMD:SOT-23-5,C7484,1
BSP75N,U903,Package_TO_SOT_SMD:SOT-223,C172450,1
TJA1051T/3,U1001,Package_SO:SOIC-8_3.9x4.9mm_P1.27mm,C38695,1
MAX13223E,U1101,Package_SO:TSSOP-20_4.4x6.5mm_P0.65mm,C118523,1

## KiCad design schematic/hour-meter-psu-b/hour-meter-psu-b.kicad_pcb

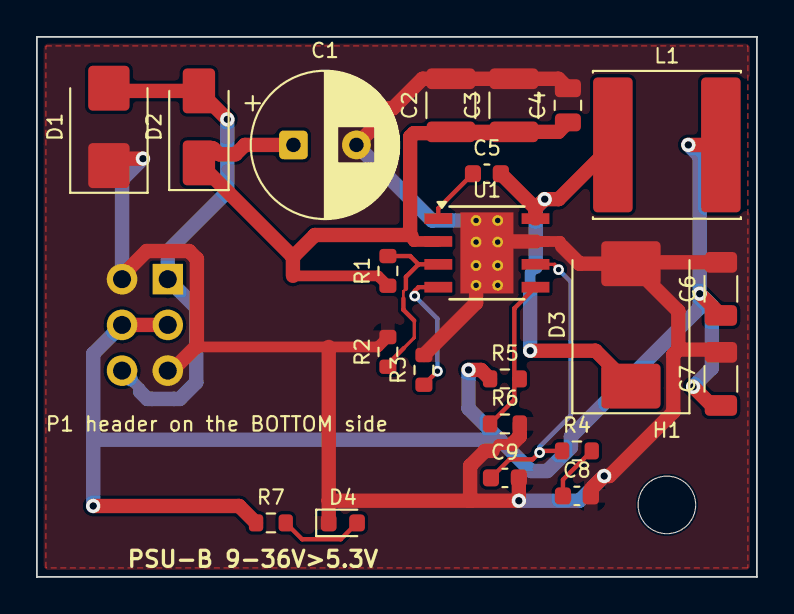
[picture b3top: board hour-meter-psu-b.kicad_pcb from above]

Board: 2 copper layers, 40.0 x 30.0 mm, 24 parts (1 on the bottom side), 12 nets.

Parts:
C1: 100uF 63V; CP_Radial_D8.0mm_P3.50mm
C2, C3: 2.2uF 100V; C_1210_3225Metric
C4: 100nF 100V; C_0805_2012Metric
C5: 100nF; C_0603_1608Metric
C6, C7: 47uF 16V; C_1206_3216Metric
C8: 6.8nF; C_0603_1608Metric
C9: 39pF; C_0603_1608Metric
D1: SMBJ36CA; D_SMB
D2: SS510; D_SMA
D3: B560C; D_SMC
D4: PWR red; LED_0603_1608Metric
H1: M3 standoff; MountingHole_3.2mm_M3
L1: 8.2uH; L_Sunlord_SWPA8040S
P1: to main J102; PinHeader_2x03_P2.54mm_Vertical
R1: 510k; R_0603_1608Metric
R2: 82k; R_0603_1608Metric
R3: 162k; R_0603_1608Metric
R4: 13k; R_0603_1608Metric
R5: 56k; R_0603_1608Metric
R6: 10k; R_0603_1608Metric
R7: 2.2k; R_0603_1608Metric
U1: TPS54360BDDAR; TI_SO-PowerPAD-8_ThermalVias

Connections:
/BOOT: C5.1, U1.1
/COMP: C9.1, R4.1, U1.6
/COMP_RC: C8.1, R4.2
/EN: R1.2, R2.1, U1.3
/FB: R5.2, R6.1, U1.5
/LED_A: D4.2, R7.2
/RT: R3.1, U1.4
/SW: C5.2, D3.1, L1.1, U1.8
/VIN: D1.2, D2.2, P1.1, P1.6
/VIN_P: C1.1, C2.1, C3.1, C4.1, D2.1, R1.1, U1.2
/VOUT: C6.1, C7.1, L1.2, P1.3, P1.4, R5.1, R7.1
GND: C1.2, C2.2, C3.2, C4.2, C6.2, C7.2, C8.2, C9.2, D1.1, D3.2, D4.1, P1.2, P1.5, R2.2, R3.2, R6.2, U1.7, U1.9

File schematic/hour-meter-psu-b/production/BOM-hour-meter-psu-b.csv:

Comment,Designator,Footprint,LCSC,Qty
100uF 63V,C1,Capacitor_THT:CP_Radial_D8.0mm_P3.50mm,C46550453,1
2.2uF 100V,"C2,C3",Capacitor_SMD:C_1210_3225Metric,C55151,2
100nF 100V,C4,Capacitor_SMD:C_0805_2012Metric,C28233,1
100nF,C5,Capacitor_SMD:C_0603_1608Metric,C14663,1
47uF 16V,"C6,C7",Capacitor_SMD:C_1206_3216Metric,C385907,2
6.8nF,C8,Capacitor_SMD:C_0603_1608Metric,C1631,1
39pF,C9,Capacitor_SMD:C_0603_1608Metric,C107049,1
SMBJ36CA,D1,Diode_SMD:D_SMB,C83326,1
SS510,D2,Diode_SMD:D_SMA,C65010,1
B560C,D3,Diode_SMD:D_SMC,C85100,1
PWR red,D4,LED_SMD:LED_0603_1608Metric,C2286,1
8.2uH,L1,Inductor_SMD:L_Sunlord_SWPA8040S,C84610,1
to main J102,P1,Connector_PinHeader_2.54mm:PinHeader_2x03_P2.54mm_Vertical,C65114,1
510k,R1,Resistor_SMD:R_0603_1608Metric,C23192,1
82k,R2,Resistor_SMD:R_0603_1608Metric,C23254,1
162k,R3,Resistor_SMD:R_0603_1608Metric,C22815,1
13k,R4,Resistor_SMD:R_0603_1608Metric,C22797,1
56k,R5,Resistor_SMD:R_0603_1608Metric,C23206,1
10k,R6,Resistor_SMD:R_0603_1608Metric,C25804,1
2.2k,R7,Resistor_SMD:R_0603_1608Metric,C4190,1
TPS54360BDDAR,U1,Package_SO:TI_SO-PowerPAD-8_ThermalVias,C524806,1
